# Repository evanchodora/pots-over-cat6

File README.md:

# POTS over CAT6 Adapter

Schematic and PCB files for an adapter board to carry 4 POTS lines over existing CAT6 cabling.

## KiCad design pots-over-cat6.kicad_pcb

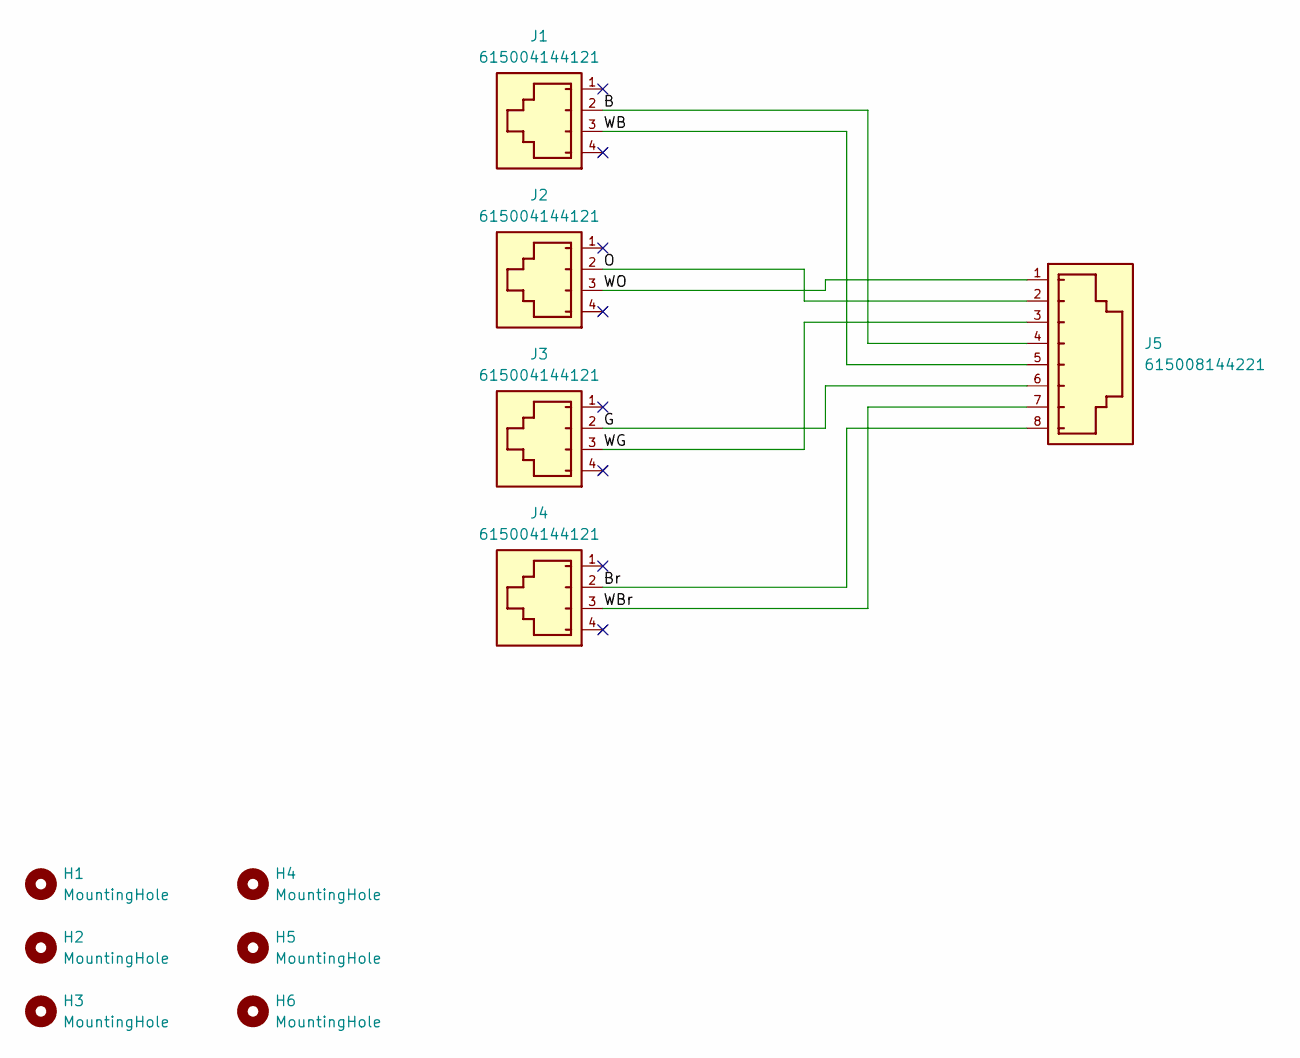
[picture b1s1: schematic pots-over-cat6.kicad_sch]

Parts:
H1, H2, H3, H4, H5, H6: MountingHole; MountingHole_2.7mm_M2.5_ISO7380
J1, J2, J3, J4: 615004144121
J5: 615008144221

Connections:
/B: J1.2, J5.4
/Br: J4.2, J5.8
/G: J3.2, J5.6
/O: J2.2, J5.2
/WB: J1.3, J5.5
/WBr: J4.3, J5.7
/WG: J3.3, J5.3
/WO: J2.3, J5.1

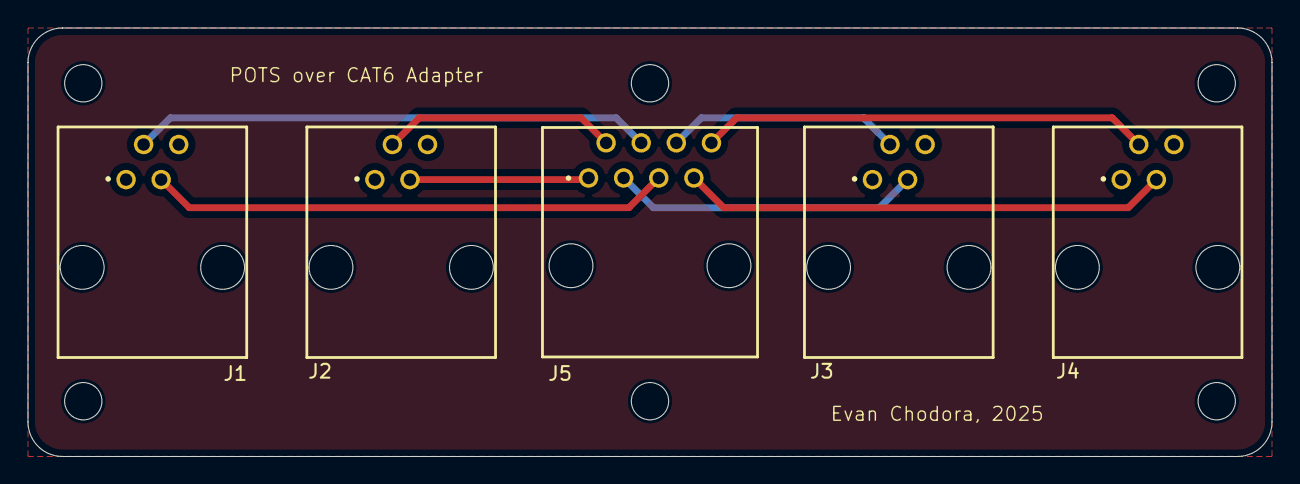
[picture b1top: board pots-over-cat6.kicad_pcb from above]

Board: 2 copper layers, 90.0 x 31.0 mm, 11 parts (0 on the bottom side), 8 nets.

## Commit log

2025-04-15 Added gerber exports
2025-04-15 Added PCB image and STEP file model
2025-04-15 Added PDF schematic
